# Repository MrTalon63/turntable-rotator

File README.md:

# Turntable Rotator

## tl;dr

- In theory amazing azimuth control step resolution of 0.02 degrees
- All parts can be 3D printed
- Uses off the shelf NEMA 17 stepper motors and drivers
- Multi-use architecture:tm:
- Universal controller board that can be used for other projects as well

In a nutshell, this project is a simple antenna rotator (could be used for photogrammetry?) that uses a belt driven turntable to rotate the azimuth of the antenna.
Elevation has not been implemented yet, but thanks to modular design you can mount an antenna on the turntable and use it as a simple rotator for azimuth only, attach fixed elevation antennas, or just slap an elevation mechanism on top of the turntable and use it as a full azimuth/elevation rotator.

### Electronics

The controller board is powered by an ESP32-S3 module, can be powered with any 9 - 40 VDC power source and supports two stepper motors and three limit switches.
You can also use servo for elevation instead, there's a pinout for that, need to supply your own power for the servo though.
The board has a USB-C port for programming and debugging.

### Software

SOFTWARE IS NOT YET IMPLEMENTED!!!
~~Commands can be sent over WiFi or UART, and the board can be configured as a WiFi access point or connect to an existing WiFi network.
The board also has a built in web server that can be used to for control, calibration and configuration, but that is also not implemented yet.~~

### Mechanical

First of all, I'm not nowhere competent in mechanical design, this is my first attempt at designing something like this, so if you have any suggestions or improvements please let me know.

The turntable is belt driven, with a 20 tooth pulley on the motor and a 120 tooth pulley on the turntable, giving a 6:1 gear ratio, which means that with a 400 step/rev (0.9 degree/step) stepper motor, we get a theoretical step resolution of 0.02 degrees, which is pretty good for a rotator of this size.
The turntable is suppported by a chungus 6910 bearing, which also allows for cable passage through the center of the turntable.

The turntable is designed to be 3D printed, and all parts can be printed on a standard 3D printer. Due to my lack of design skills, you'd want pretty accurate printer, as the tolerances can get pretty tight, especially for the bearing and screw holes.

### Future Work

- [ ] Redesign the turntable, it was the first part I designed and it shows, the Fusion timeline is a mess and a single change just breaks everything.
- [ ] Design an elevation mechanism, maybe a simple belt driven one, or maybe a servo driven one, not sure yet.
- [ ] Implement the software, need working PCB first.
- [ ] Design pole mount, maybe a simple clamp on design, or maybe a tripod mount, not sure yet.

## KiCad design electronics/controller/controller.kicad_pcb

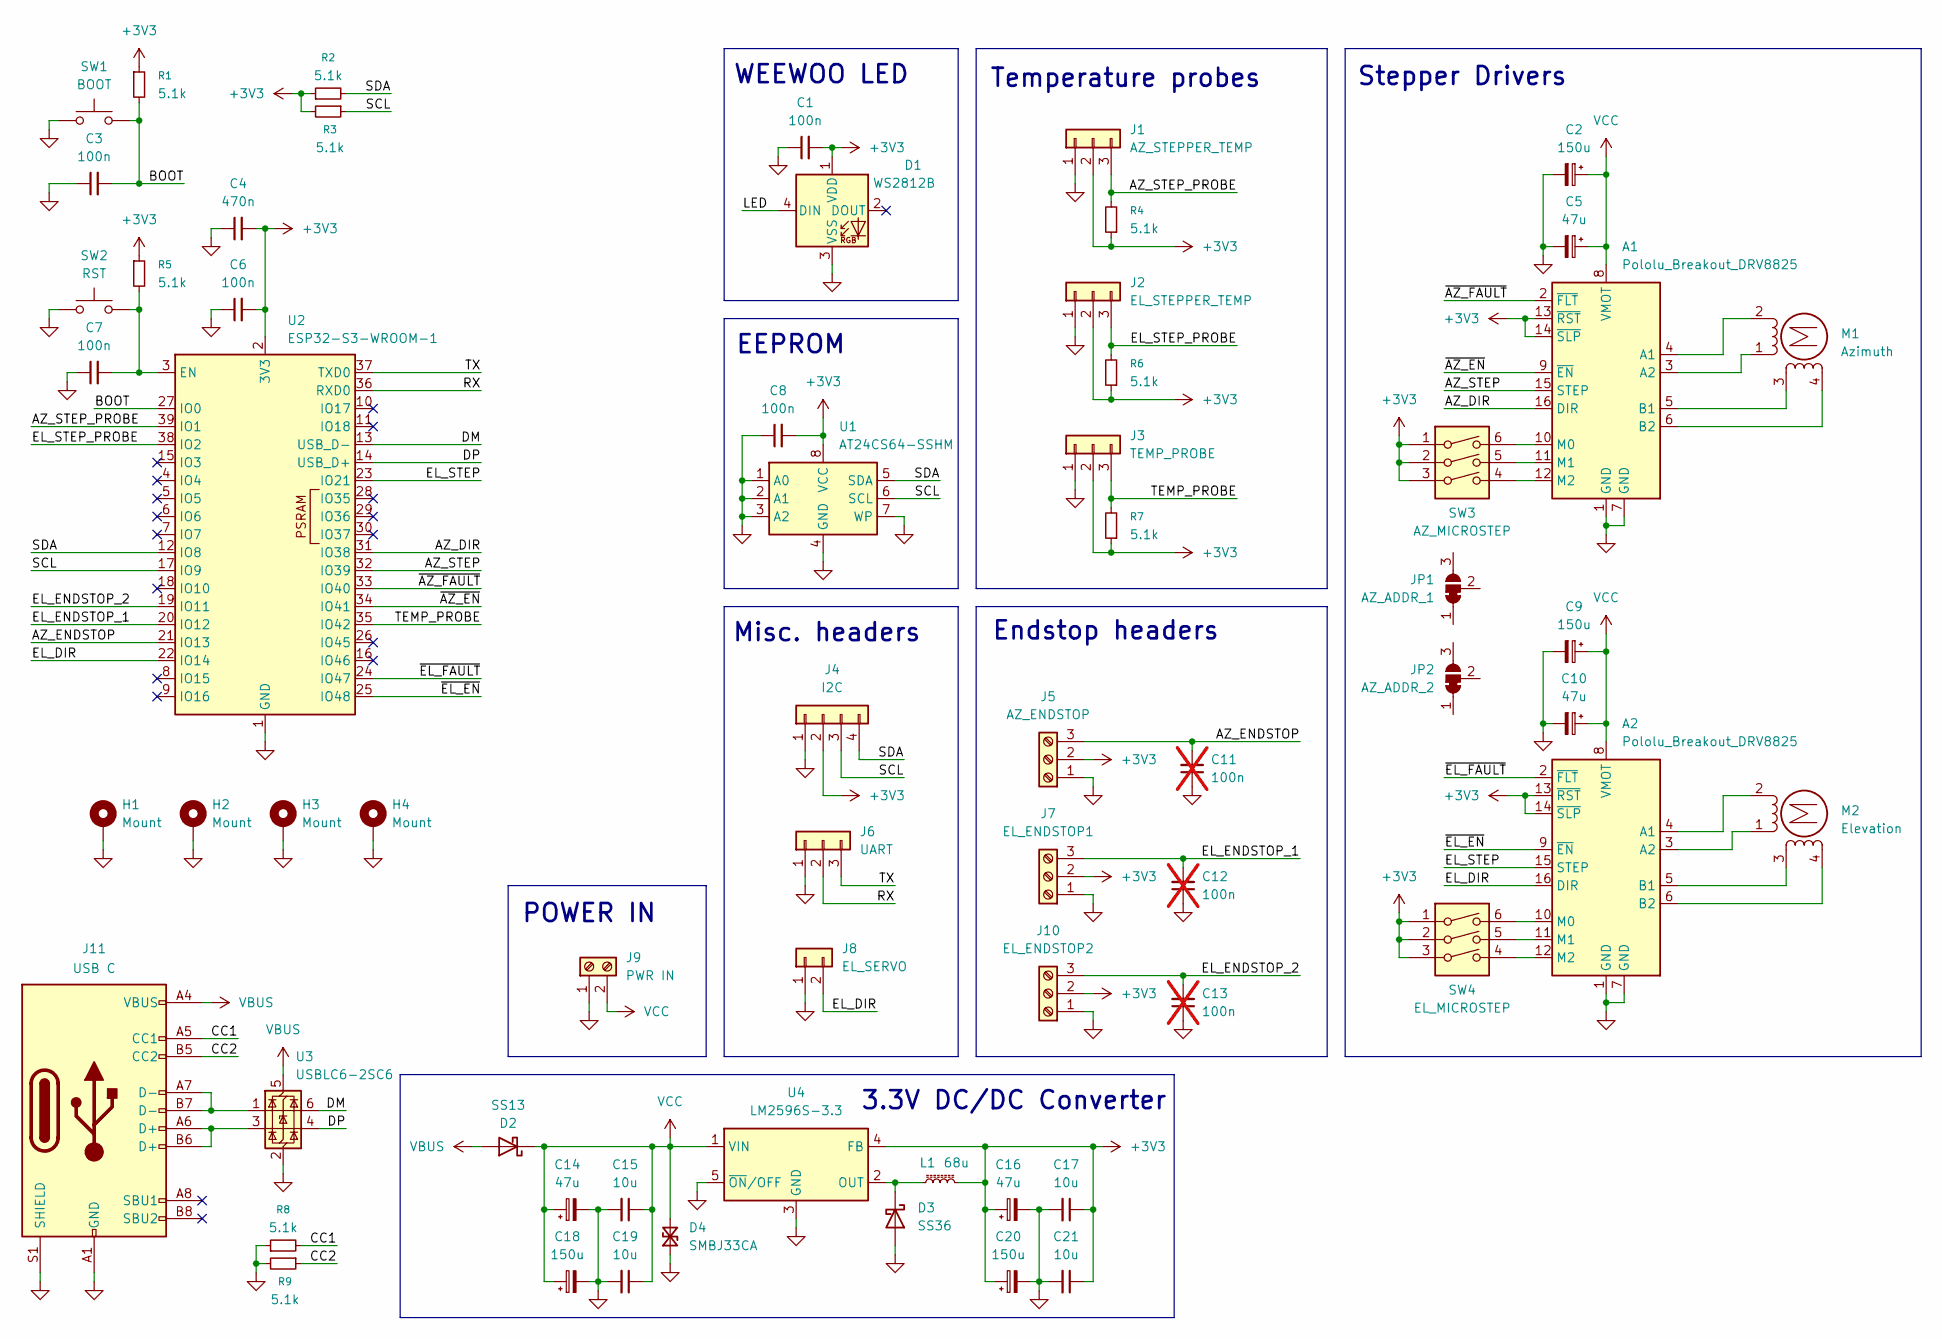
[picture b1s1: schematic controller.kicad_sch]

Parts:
A1, A2: Pololu_Breakout_DRV8825; Pololu_Breakout-16_15.2x20.3mm
C1, C3, C6, C7, C8: 100n; C_0402_1005Metric
C2, C9, C18, C20: 150u; CP_Elec_10x10
C4: 470n; C_0402_1005Metric
C5, C10, C14, C16: 47u; CP_Elec_8x10
C11, C12, C13: 100n; C_0603_1608Metric_Pad1.08x0.95mm_HandSolder; not fitted
C15, C17, C19, C21: 10u; C_1210_3225Metric
D1: WS2812B; LED_WS2812B_PLCC4_5.0x5.0mm_P3.2mm
D2: SS13; D_SMA
D3: SS36; D_SMA
D4: SMBJ33CA; D_SMB
H1, H2, H3, H4: Mount; MountingHole_2.7mm_M2.5_DIN965_Pad
J1: AZ_STEPPER_TEMP; PinHeader_1x03_P2.54mm_Vertical
J2: EL_STEPPER_TEMP; PinHeader_1x03_P2.54mm_Vertical
J3: TEMP_PROBE; PinHeader_1x03_P2.54mm_Vertical
J4: I2C; PinHeader_1x04_P2.54mm_Vertical
J5: AZ_ENDSTOP; TerminalBlock_MaiXu_MX126-5.0-03P_1x03_P5.00mm
J6: UART; PinHeader_1x03_P2.54mm_Vertical
J7: EL_ENDSTOP1; TerminalBlock_MaiXu_MX126-5.0-03P_1x03_P5.00mm
J8: EL_SERVO; PinHeader_1x02_P2.54mm_Vertical
J9: PWR IN; TerminalBlock_MaiXu_MX126-5.0-02P_1x02_P5.00mm
J10: EL_ENDSTOP2; TerminalBlock_MaiXu_MX126-5.0-03P_1x03_P5.00mm
J11: USB C; USB_C_Receptacle_GCT_USB4105-xx-A_16P_TopMnt_Horizontal
JP1: AZ_ADDR_1; SolderJumper-3_P1.3mm_Bridged12_RoundedPad1.0x1.5mm_NumberL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
JP2: AZ_ADDR_2; SolderJumper-3_P1.3mm_Bridged12_RoundedPad1.0x1.5mm_NumberL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
L1: 68u; L_Coilcraft_MSS1260-XXX
M1: Azimuth; TerminalBlock_MaiXu_MX126-5.0-04P_1x04_P5.00mm
M2: Elevation; TerminalBlock_MaiXu_MX126-5.0-04P_1x04_P5.00mm
R1, R2, R3, R4, R5, R6, R7, R8, R9: 5.1k; R_0402_1005Metric
SW1: BOOT; KLS7TS6611
SW2: RST; KLS7TS6611
SW3: AZ_MICROSTEP; SW_DIP_SPSTx03_Slide_KingTek_DSHP03TJ_W5.25mm_P1.27mm_JPin
SW4: EL_MICROSTEP; SW_DIP_SPSTx03_Slide_KingTek_DSHP03TJ_W5.25mm_P1.27mm_JPin
U1: AT24CS64-SSHM; TSSOP-8_4.4x3mm_P0.65mm
U2: ESP32-S3-WROOM-1
U3: USBLC6-2SC6; SOT-23-6
U4: LM2596S-3.3; TO-263-5_TabPin3

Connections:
/AZ_DIR: A1.16 (DIR), U2.31 (IO38)
/AZ_ENDSTOP: C11.2, J5.3, U2.21 (IO13)
/AZ_STEP: A1.15 (STEP), U2.32 (IO39)
/AZ_STEP_PROBE: J1.3, R4.2, U2.39 (IO1)
/BOOT: C3.2, R1.2, SW1.2, U2.27 (IO0)
/CC1: J11.A5 (CC1), R8.2
/CC2: J11.B5 (CC2), R9.1
/DM: U2.13 (USB_D-), U3.6 (I/O1)
/DP: U2.14 (USB_D+), U3.4 (I/O2)
/EL_DIR: A2.16 (DIR), J8.2, U2.22 (IO14)
/EL_ENDSTOP_1: C12.2, J7.3, U2.20 (IO12)
/EL_ENDSTOP_2: C13.2, J10.3, U2.19 (IO11)
/EL_STEP: A2.15 (STEP), U2.23 (IO21)
/EL_STEP_PROBE: J2.3, R6.2, U2.38 (IO2)
/LED: D1.4 (DIN)
/RX: J6.2, U2.36 (RXD0)
/SCL: J4.3, R3.1, U1.6 (SCL), U2.17 (IO9)
/SDA: J4.4, R2.2, U1.5 (SDA), U2.12 (IO8)
/TEMP_PROBE: J3.3, R7.2, U2.35 (IO42)
/TX: J6.3, U2.37 (TXD0)
/~AZ_EN: A1.9 (~EN), U2.34 (IO41)
/~AZ_FAULT: A1.2 (~FLT), U2.33 (IO40)
/~EL_EN: A2.9 (~EN), U2.25 (IO48)
/~EL_FAULT: A2.2 (~FLT), U2.24 (IO47)
unnamed: A1.4 (A1), M1.2 (-)
unnamed: A1.3 (A2), M1.1
unnamed: A1.5 (B1), M1.3
unnamed: A1.6 (B2), M1.4
unnamed: A1.10 (M0), SW3.6
unnamed: A1.11 (M1), SW3.5
unnamed: A1.12 (M2), SW3.4
unnamed: A2.4 (A1), M2.2 (-)
unnamed: A2.3 (A2), M2.1
unnamed: A2.5 (B1), M2.3
unnamed: A2.6 (B2), M2.4
unnamed: A2.10 (M0), SW4.6
unnamed: A2.11 (M1), SW4.5
unnamed: A2.12 (M2), SW4.4
unnamed: D3.1 (K), L1.1, U4.2 (OUT)
unnamed: J11.A6 (D+), J11.B6 (D+), U3.3 (I/O2)
unnamed: J11.A7 (D-), J11.B7 (D-), U3.1 (I/O1)
unnamed: C7.2, R5.2, SW2.2, U2.3 (EN)
VBUS: D2.2 (A), J11.A4 (VBUS), J11.A9 (VBUS), J11.B4 (VBUS), J11.B9 (VBUS), U3.5 (VBUS)

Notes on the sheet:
EEPROM
Endstop headers
3.3V DC/DC Converter
Misc. headers
POWER IN
Stepper Drivers
WEEWOO LED
Temperature probes

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
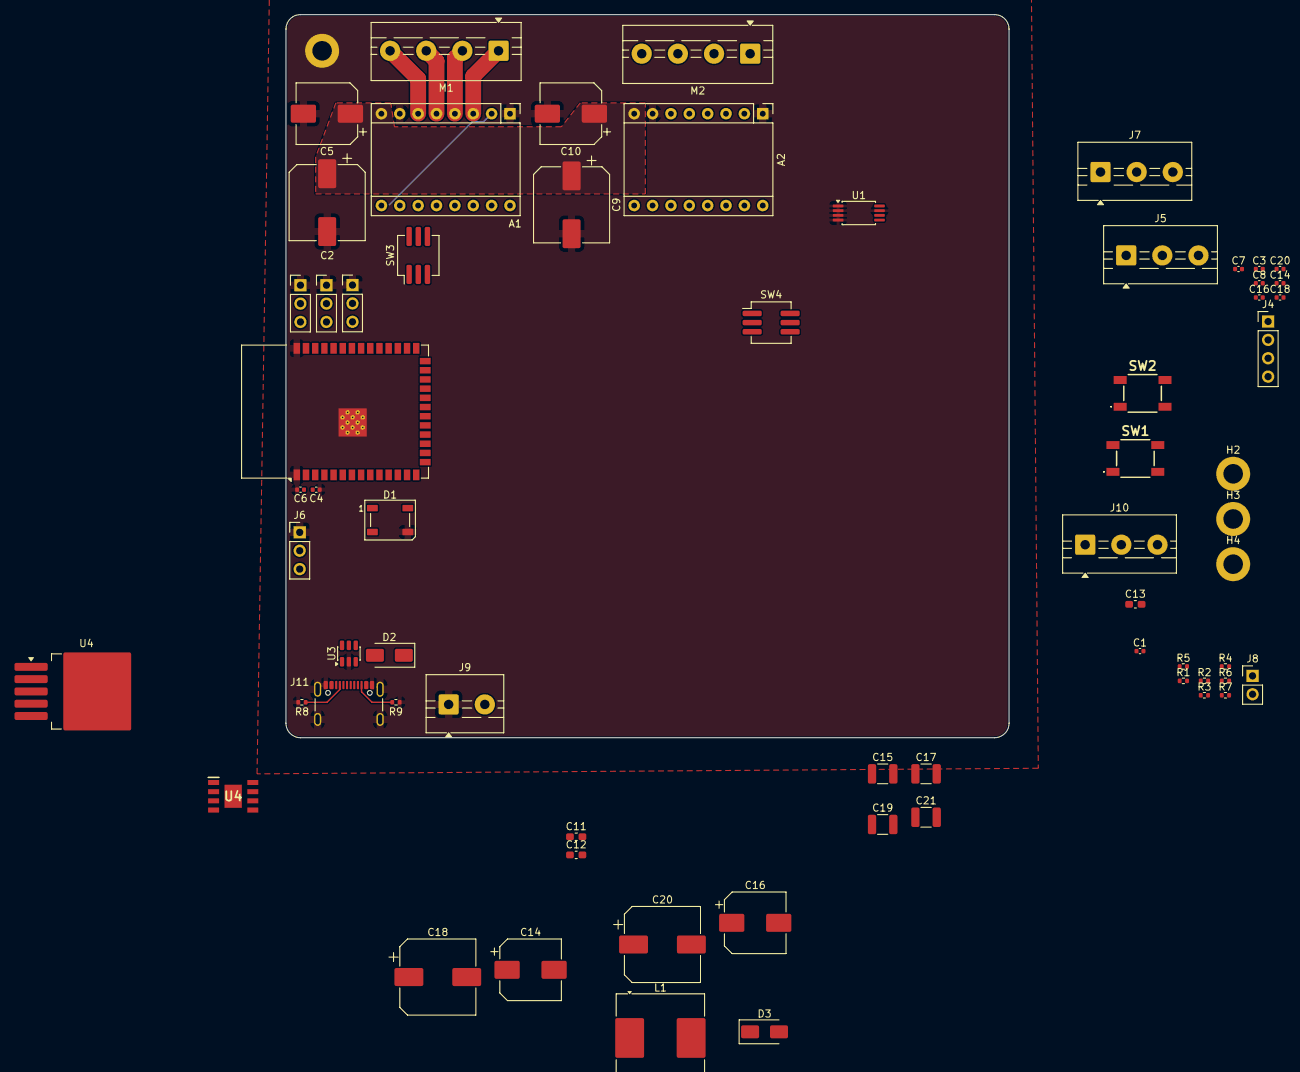
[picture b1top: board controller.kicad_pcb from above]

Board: 2 copper layers, 100.0 x 100.0 mm, 66 parts (0 on the bottom side), 45 nets.

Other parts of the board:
C14#2: 47u; CP_Elec_8x10
C16#2, C20#2: 100n; C_0402_1005Metric
C18#2: 150u; CP_Elec_10x10
U4#2: BD433S5EFJ-CE2; SOIC127P600X100-9N

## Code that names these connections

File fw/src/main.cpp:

#include <Arduino.h>
#include <FastAccelStepper.h>
#include <TMCStepper.h>

#define AZ_DIR_PIN 5
#define AZ_STEP_PIN 6
#define AZ_EN_PIN 2137
#define AZ_CS_PIN 2137
#define R_SENSE 0.11f // Idfk that's what is in example

TMC2130Stepper azDriver(AZ_CS_PIN, R_SENSE);
FastAccelStepperEngine engine = FastAccelStepperEngine();
FastAccelStepper *azStepper = NULL;

void setup() {
  Serial.begin(115200);
  delay(5000); // Wait for USB Serial because it sucky
  Serial.println("Setting up...");
  Serial.println("ESP SDK version: " + String(esp_get_idf_version()));

  SPI.begin();
  azDriver.begin();
  azDriver.toff(5);
  azDriver.rms_current(600); // mA
  azDriver.microsteps(16);

  // Enable sum fancy shit, allegedly stepper should be silky smooth
  azDriver.en_pwm_mode(true);
  azDriver.pwm_autoscale(true);

  engine.init();
  Serial.println("Engine initialized.");
  azStepper = engine.stepperConnectToPin(AZ_STEP_PIN, DRIVER_I2S_DIRECT);

  if (azStepper) {
    Serial.println("Stepper connected to pin.");
  } else {
    Serial.println("Failed to connect stepper to pin.");
    while (1); // Halt execution
  }

  azStepper->setDirectionPin(AZ_DIR_PIN);
  azStepper->setSpeedInUs(10);
  azStepper->setAcceleration(1000);
}

void loop() {
  if (Serial.available()) {
    String input = Serial.readStringUntil('\n');
    input.trim();
    int space = input.indexOf(' ');
    String command;
    String value;
    if (!space) {
      command = input; //no val
      value = "";
    } else {
      command = input.substring(0, space);
      value = input.substring(space + 1);
      value.trim();
    }
    command.toLowerCase();

    if (command == "f" || command == "forward") {
      if (value.isEmpty()) {
        Serial.println("Moving forward...");
        azStepper->runForward();
      } else {
        uint32_t steps = value.toInt();
        Serial.println("Moving forward " + String(steps) + " steps...");
        azStepper->move(steps);
      }

    } else if (command == "b" || command == "backward") {
      if (value.isEmpty()) {
        Serial.println("Moving backward...");
        azStepper->runBackward();
      } else {
        uint32_t steps = value.toInt();
        Serial.println("Moving backward " + String(steps) + " steps...");
        azStepper->move(-steps);
      }

    } else if (command == "s" || command == "speed") {
      if (value.isEmpty()) {
        Serial.println("Current speed: " + String(azStepper->getCurrentSpeedInUs()) + " us/step.");
      } else {
        uint32_t speed = value.toInt();
        azStepper->setSpeedInUs(speed);
        Serial.println("Speed set to " + String(speed) + " us/step.");
      }

    } else if (command == "a" || command == "acceleration") {
      if (value.isEmpty()) {
        Serial.println("Current acceleration: " + String(azStepper->getAcceleration()) + " steps/s^2.");
      } else {
        uint32_t accel = value.toInt();
        azStepper->setAcceleration(accel);
        Serial.println("Acceleration set to " + String(accel) + " steps/s^2.");
      }

    } else if (command == "l" || command == "stop") {
      Serial.println("Stopping...");
      azStepper->stopMove();

    } else if (command == "status") {
      Serial.println("Current status:");
      Serial.println("  Speed: " + String(azStepper->getCurrentSpeedInUs()) + " us/step");
      Serial.println("  Acceleration: " + String(azStepper->getAcceleration()) + " steps/s^2");
      Serial.println("  Current position: " + String(azStepper->getCurrentPosition()) + " steps");
    
    } else if (command == "h" || command == "help") {
      Serial.println("Available commands:");
      Serial.println("  f [steps] - Move forward (optional steps)");
      Serial.println("  b [steps] - Move backward (optional steps)");
      Serial.println("  s [speed] - Set speed in us/step or get current speed");
      Serial.println("  a [accel] - Set acceleration in steps/s^2 or get current acceleration");
      Serial.println("  l         - Stop movement");
      Serial.println("  status    - Show current status");
      Serial.println("  h         - Show this help message");
    }

    else {
      Serial.println("Unknown command: " + command);
    }
  }
}

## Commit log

2026-03-15 Finished controller schematic
2026-03-15 Add yapping in readme
2026-03-15 Add Fusion files
2026-03-15 Switch to Buck converter
2026-03-18 PlatformIO firmware
2026-03-18 Add mounting holes to the schematic
2026-03-19 test firmware
2026-03-20 TMC2130 software config
